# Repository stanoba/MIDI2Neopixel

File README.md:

# MIDI2Neopixel - Piano LED Visualizer

MIDI2Neopixel is simple Piano LED Visualizer based on Arduino pro micro (Leonardo) and LED strip WS2812B (144 LEDs / 1 m). It's compatible with [Synthesia](https://www.synthesiagame.com) piano learning software. 

In general, it could be also used with any music software allowing to define MIDI out device (e.g. NI Kontakt). 

## Hardware

See <a href="./Hardware">Hardware</a> README.md for more info.

## Software

See <a href="./Software">Software</a> README.md for more info.

## 3D printed parts

See <a href="./3D models">3D models</a> README.md for more info.

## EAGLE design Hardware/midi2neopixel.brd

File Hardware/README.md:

# MIDI2Neopixel - Piano LED Visualizer - Hardware

Electronic is built on **Arduino pro micro** (Atmega 32u4) which behave as MIDI output device. It could be powered from 5V DC adapter or directly from USB port (limited amperage) after soldering schottky diode between Arduino PWR pin and + terminal of capacitor. LEDs used in project are WS2812B (144 LEDs / 1 m).

PCB has place for SMD 0603 components or classic THT (You can select based on your supplies).

---
## Breadboard Example

---
## Schematic

## PCB

PCB was designed in Eagle 9.6.2:

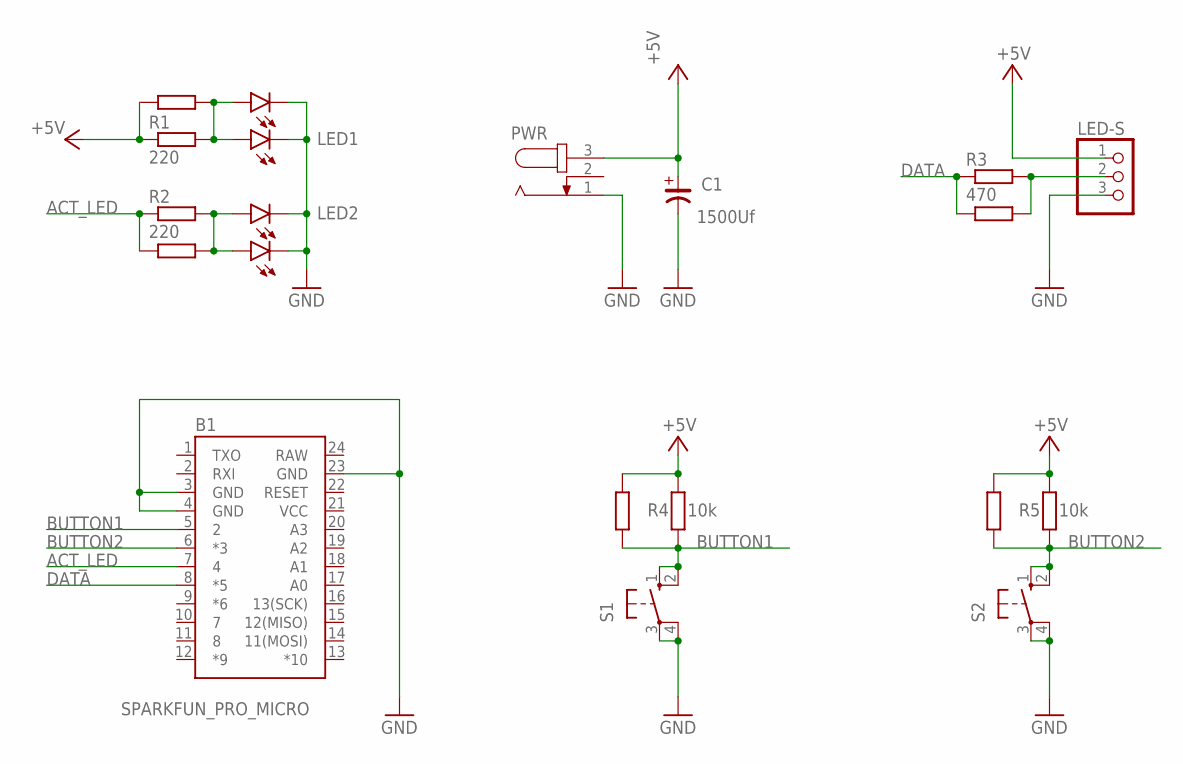
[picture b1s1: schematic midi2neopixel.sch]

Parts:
B1: SPARKFUN_PRO_MICRO
C1: 1500Uf; CEH-050-100X200
LED1: Green; LED3MM
LED2: Red; LED3MM
LED-S: PINHD-1X3; 1X03
LEDX1, LEDX2: LEDSML0603; SML0603
PWR: JACK-PLUG0; SPC4077
R1, R2: 220; 0207/7
R3: 470; 0207/7
R4, R5: 10k; 0207/7
RR1, RR2: 220; R0603
RR3: 470; R0603
RR4, RR5: 10k; R0603
S1, S2: 10-XX; B3F-10XX

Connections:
+5V: C1.+, LED-S.1, PWR.3, R1.1, R4.2, R5.2, RR1.1, RR4.2, RR5.2
ACT_LED: B1.7 (4), R2.1, RR2.1
BUTTON1: B1.5 (2), R4.1, RR4.1, S1.1 (S), S1.2 (S1)
BUTTON2: B1.6 (*3), R5.1, RR5.1, S2.1 (S), S2.2 (S1)
DATA: B1.8 (*5), R3.1, RR3.1
GND: B1.3 (GND), B1.4 (GND), B1.23 (GND), C1.-, LED1.K (C), LED2.K (C), LED-S.3, LEDX1.C, LEDX2.C, PWR.1, S1.3, S1.4 (P1), S2.3, S2.4 (P1)
unnamed: LED-S.2, R3.2, RR3.2
unnamed: LED1.A, LEDX1.A, R1.2, RR1.2
unnamed: LED2.A, LEDX2.A, R2.2, RR2.2
RAW: B1.24 (RAW)
VCC: B1.21 (VCC)

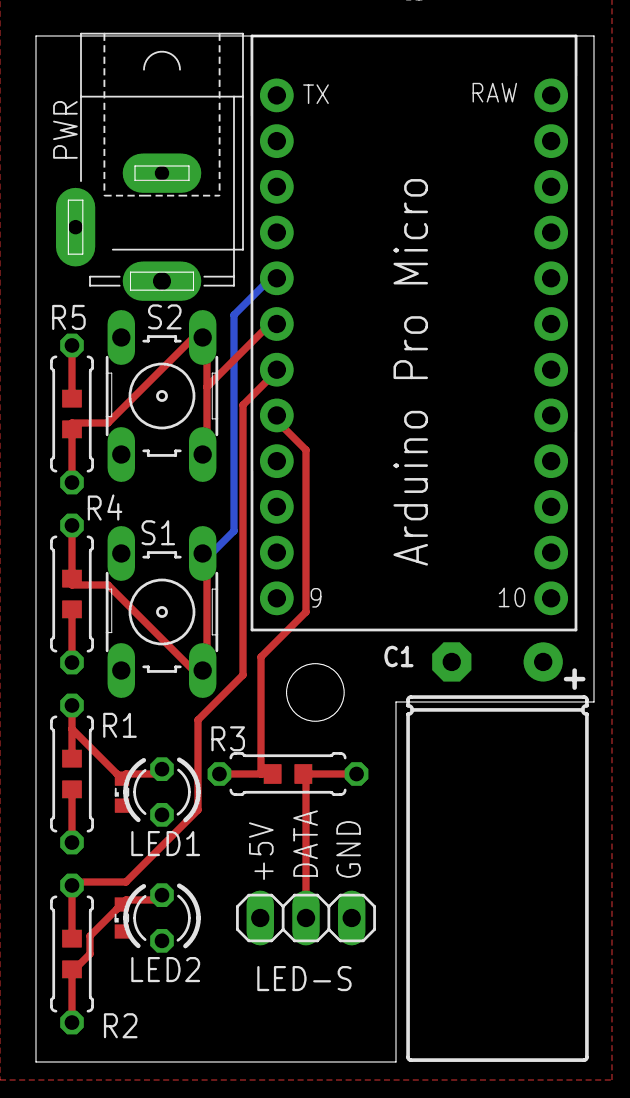
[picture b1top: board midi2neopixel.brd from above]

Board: 2 copper layers, 31.0 x 57.0 mm, 20 parts (0 on the bottom side), 9 nets.

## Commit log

2021-01-08 First upload
2021-01-09 Fritzing example
2021-01-15 Extended debug msg.
2023-01-02 'if(DEBUG' to '#ifdef DEBUG'
2023-01-03 Add start decoration

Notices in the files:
parts and their libraries:
SparkFun-Boards: Licensing: Creative Commons ShareAlike 4.0 International - https://creativecommons.org/licenses/by-sa/4.0
rc-master: Copyright (C) 2007, Bob Starr
